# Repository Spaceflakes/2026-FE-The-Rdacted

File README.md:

# WRO-2026

# The Redacted

**The official repository of The Redacted for WRO - Future Engineers 2026**

## Content

### Folders
- **Engineering Manual:** Official manual of team The Redacted for WRO FE 26 (manual.pdf). Contains component selection, CAD, PCB schematics, and assembly guides.
- **PCBA:** Complete set of KiCad PCB files, manufacturing outputs (Gerbers), interactive HTML BOM, and documentation.
- **t-photos:** Team photos (1 formal, 2 informal).
- **v-photos:** 6 photos of the vehicle (front, back, left, right, top, bottom).
- **video:** video.md file with the official vehicle demonstration video link.
- **schemes:** Schematic diagrams, motor connections, power distribution, and 3D PCB renders.
- **src:** ROS 2 control software nodes (motion, LiDAR, camera/vision, parking logic).
- **models:** 3D CAD model files (STEP format).

### Index
- [The Redacted](#the-redacted)
- [Vehicle Photos and Video](#vehicle-photos-and-video)
- [Hardware Materials](#hardware-materials)
- [Mobility Management](#mobility-management)
- [Design](#design)
- [Power Management and Sense Management](#power-management-and-sense-management)
- [Schematic Diagram](#schematic-diagram)
- [Obstacle Management](#obstacle-management)
- [Our Journal](#our-journal)
- [Gantt Chart](#gantt-chart)

---

## The Redacted

### Members
1. **Anvay Jain**  
   Grade 9, The Sanskaar Valley School. Head of this repository. Interested in Space, Science, KSP, and Mathematics.
2. **Siddesh Jain**  
   12th Grader, Billabong High International School. Lead engineer/development head. CAD, hardware, system architecture.
3. **Prayash**  
   Co-engineer and robotics developer. Software integration, testing, and mechanical assembly.

### Team Pictures
#### Formal

#### Informal

---

# Vehicle Photos and Video

### Photos
Vehicle photographs showing all 6 sides are available in the [/v-photos](./v-photos) folder.

### Videos
The demonstration video link and operational breakdown are located in [/video/video.md](./video/video.md).

---

## Hardware Materials

| Name | Link |
| :--- | :--- |
| Rpi 4B/5 | [Link](https://www.raspberrypi.com/products/raspberry-pi-5) |
| LiDAR | [Link](https://robu.in/product/ydlidar-x4-pro-360-degree-ros-scanner-for-navigation-collision-avoidance-10m/#tab-specification) |
| Servo | [Link](https://robu.in/product/surpass-hobby-25kg-s2500m-servo/) |
| Wheels | [Link](https://robu.in/product/65mm-robot-smart-car-12-rim-wheel-blue/) |
| Pi Camera | [Link](https://robu.in/product/arducam-8mp-imx219-175-degree-ultra-wide-angle-raspberry-pi-camera-module-compatible-with-raspberry-pi-4-model-b-pi-3-3b-and-pi-zero-2w/) |
| Custom 2026 WRO Hat PCB | [Link](https://github.com/The-Redacted/WRO-2026/tree/main/PCBA) |
| ESC + Motor | [Link](https://www.hobbywingdirect.com/collections/quicrun-brushless-system/products/quicrun-wp-10bl120-sl-system-g2?variant=41474386854003) |
| Battery | 2x DOGCOM 4S 850 mAh 150C LiPo |
| Gears | Custom 3D Printed Bevel Gears |
| PCB Components | TI LM61460 (5.15V @ 6A) & TPS62932 (8V @ 2A) |
| Carbon Fiber Stock | 12mm OD x 10mm ID Tubes & 3mm OD Rods |

### PCB Design & Prototype PCB
#### Prototype PCB
- **Issue:** Standard 5.0V buck converters caused under-voltage warnings on the Pi 4B under load.
- **Solution:** Designed 2026 WRO Hat for a stabilized 5.15V rail at 6A using the TI LM61460.
- **LC Hot-Plug Fix:** Added a 1000 µF electrolytic capacitor between switch output and GND to dissipate inrush energy and prevent voltage ringing.

#### PCB Design
- **4-Layer Stackup:**
    - Layer 1: High-speed switching/control.
    - Layer 2: Ground plane.
    - Layer 3: Power planes (BATT, 5.15V, 8.0V).
    - Layer 4: Ground plane and secondary signals.

---

## Mobility Management
- **Drive System:** Surpass Hobby 3674 1700KV brushless motor + 120A 4S ESC.
- **Differential Gearbox:** 3D-printed, 2:7 gear reduction ratio.
- **Steering:** Direct-drive Ackerman system with S2500M 25 kg-cm servo on 8V rail.
- **Bearing/Axle Support:** Needle roller/thrust bearings for front knuckles; carbon fiber tubes for rear axles.

---

## Design
- **Wheelbase:** 184.3 mm.
- **Width:** <180 mm.
- **Height:** <80 mm.
- **Chassis:** Carbon fiber rods for structural rigidity.

---

## Power Management and Sense Management

### Power Management
- **Battery:** 2x DOGCOM 4S 850 mAh LiPo in parallel (1700 mAh total).
- **5.15V Rail:** TI LM61460 (6A) for RPi 4B and LiDAR.
- **8.0V Rail:** TI TPS62932 (2A) for steering servo.

### Sense Management
- **YD-LiDAR X4 Pro:** 360° 2D Laser Range Finder for mapping/navigation.
- **Arducam IMX219:** 175° FOV camera for pillar color classification.

---

## Schematic Diagram
- **Power Input:** XT30 connector (14.8V–16.8V).
- **Interfaces:** RPi 4B GPIO, USB (LiDAR), CSI (Camera), Expansion Ports (ToF sensors).

---

## Obstacle Management

### Strategy
Uses ROS 2 for modularity, combining LiDAR for 3D mapping and Camera for 2D pillar color classification.

### Logic
- **Round 1 (Open):** Wall-following via LiDAR and lane maintenance.
- **Round 2 (Obstacle):** Pillar detection -> Camera classification -> Dynamic path planning.
- **Parking:** Automated sequence using LiDAR/Camera boundary detection and PID feedback.

---

## Our Journal
- **June:** Strategy, sensing evaluation, concept sketches.
- **July:** CAD modeling, PCB design, tire molding, printing.
- **August:** Assembly, PCB reflow, ROS 2 software development, documentation.

**The journal is one of the most detailed description and accounts for all the decision made. It should most definitely be read.**

---

## Gantt Chart

| Task / Milestone | June | July | August |
| :--- | :--- | :--- | :--- |
| Concept & Selection | X | | |
| 3D CAD Modeling | | X | |
| KiCad PCB Design | | X | |
| SLA Tire Molds | | X | |
| 3D Print & Assembly | | X | X |
| PCB & Reflow | | | X |
| ROS 2 Software | | | X |
| Integration & Testing | | | X |

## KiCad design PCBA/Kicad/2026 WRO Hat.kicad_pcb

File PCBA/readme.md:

# PCB Design Files

This directory contains the complete set of KiCad Printed Circuit Board (PCB) files, manufacturing outputs, and documentation required to view, modify, assemble, and produce this board.
---

## Directory Contents

Here is a quick overview of the essential files included in this folder:

| File / Folder Name | Type | Description |
| --- | --- | --- |
| **`interactive bom.html`** | HTML | Interactive Bill of Materials tool for easy manual assembly and component placement. |
| **`PCB BOM.csv`** | CSV | The complete, standard Bill of Materials listing all required electronic components, values, and footprints. |
| **`PCB_Schematic.pdf`** | PDF | A high-resolution PDF export of the circuit schematic for quick reference without needing CAD software. |
| **`KiCAD/production/WRO_Hat_V1.5.zip`** | ZIP Archive | The compiled Gerber and Drill files, ready to be uploaded to your favorite PCB manufacturer. |
| **KiCad Source Files** | KiCad | The raw `.kicad_pro`, `.kicad_sch`, and `.kicad_pcb` files for editing the design. |

---

## Detailed File Breakdown

### 1. The Interactive BOM (`interactive bom.html`)

This is a highly useful tool generated by the **InteractiveHtmlBom** plugin. If you plan on soldering this board yourself, simply open this file in any modern web browser. It provides a visual representation of the PCB, allowing you to highlight components, track your progress, and see exactly where each part belongs.

### 2. Standard Bill of Materials (`PCB BOM.csv`)

If you are ordering parts from suppliers like DigiKey, Mouser, or LCSC, this CSV file is your go-to resource. It contains a tabular breakdown of every resistor, capacitor, IC, and connector required.

### 3. Manufacturing Gerbers (`WRO_Hat_V1.5.zip`)

This ZIP archive contains all the industry-standard RS-274X Gerber files and Excellon drill files required by board houses (such as JLCPCB, PCBWay, or OSH Park).

* **Location:** Navigate to the `KiCAD/production/` folder to find this archive.
* **Usage:** Simply upload the `.zip` file directly to the manufacturer's quote page.

### 4. Schematic Reference (`PCB_Schematic.pdf`)

For software engineers writing firmware or hardware reviewers checking pinouts, the PDF schematic offers a clean, easily readable map of the entire circuit. It is fully searchable, making it easy to trace specific signals or power rails.

---

## Getting Started with KiCad

If you want to view or modify the raw board design:

1. Ensure you have the latest version of **KiCad EDA** installed on your system.
2. Clone or download this repository to your local machine.
3. Open the `.kicad_pro` project file in the main directory.
4. Launch the **Schematic Editor** or **PCB Editor** directly from the KiCad project manager.

---

> Important Note: Before sending the Gerber files for manufacturing, please verify that the design meets your specific board house's capabilities and tolerances (minimum trace width, hole size, and clearance).

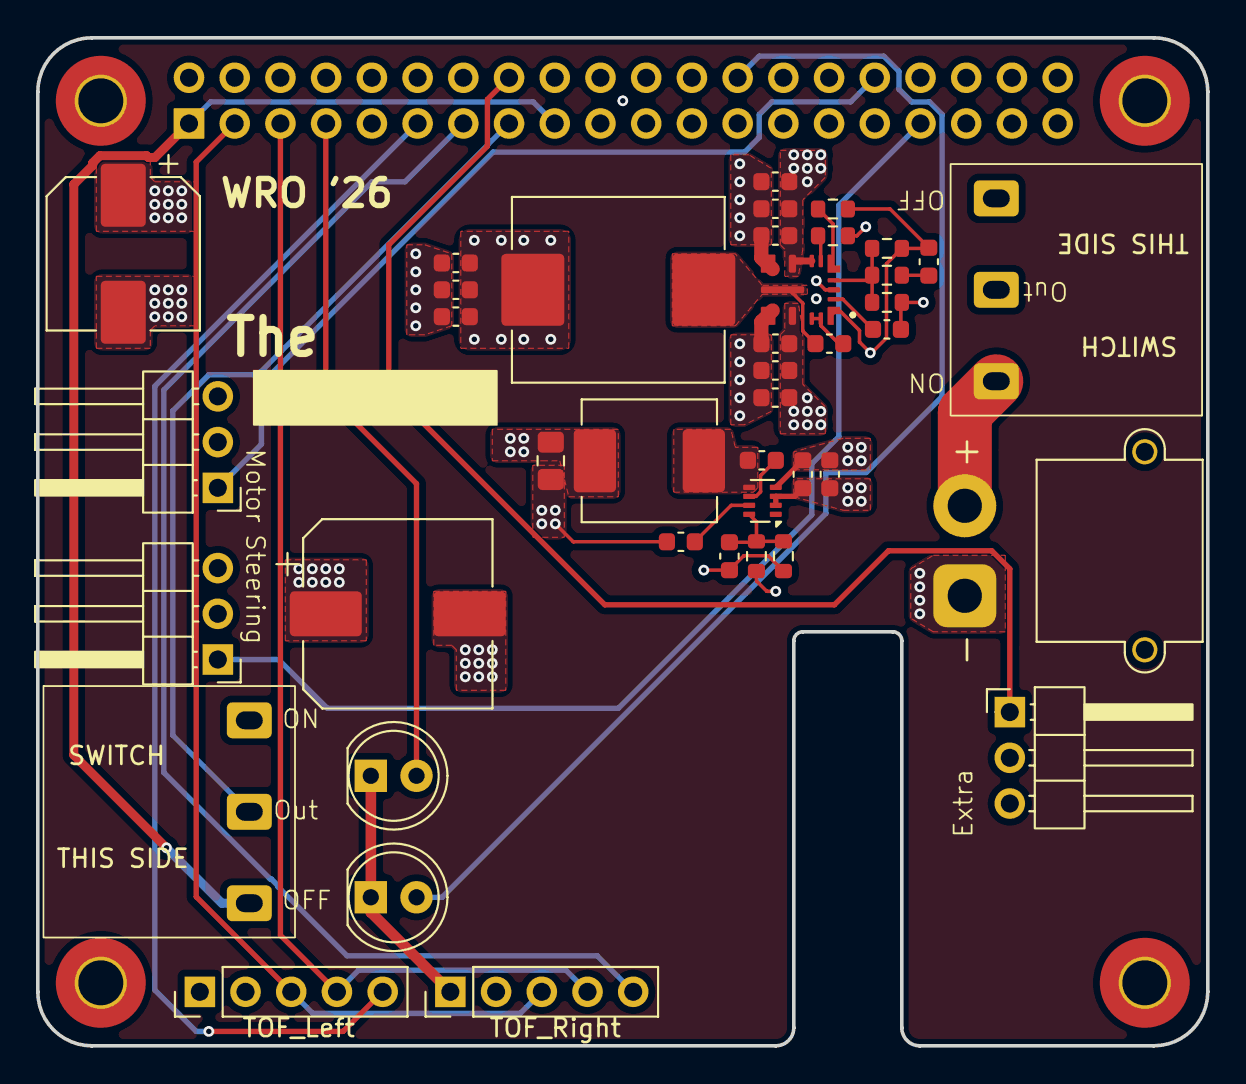
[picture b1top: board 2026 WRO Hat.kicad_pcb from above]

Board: 4 copper layers, 65.0 x 56.0 mm, 46 parts (1 on the bottom side), 27 nets.

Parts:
C1, C2, C3, C4: 4.7u; C_0603_1608Metric
C5, C6, C7: 47u; C_0603_1608Metric
C8, C9: 220n; C_0603_1608Metric
C10: 1u; C_0603_1608Metric
C11: 1p; C_0603_1608Metric
C12, C14, C16: 100n; C_0603_1608Metric
C13: 10u; C_0603_1608Metric
C15: 33n; C_0603_1608Metric
C17: 12p; C_0603_1608Metric
C18: 47u; C_0805_2012Metric_Pad1.18x1.45mm_HandSolder
C19: 220u; CP_Elec_8x10
C20: 270u; CP_Elec_10x10
D1, D2: LED; LED_D5.0mm
H1, H2, H3, H4: MountingHole; MountingHole_2.5mm_Pad_TopBottom
J1: Raspberry_Pi_4; PinSocket_2x20_P2.54mm_Vertical
J2: XT30_Power; AMASS_XT30PW-M_1x02_P2.50mm_Horizontal
J3: TOF_Right; PinHeader_1x05_P2.54mm_Vertical
J4: TOF_Left; PinHeader_1x05_P2.54mm_Vertical
L1: 6.8u; L_Chilisin_BMRF00101040
L2: 15u; L_Chilisin_BMRB00060618
M1: Throttle; PinHeader_1x03_P2.54mm_Horizontal
M2: Steering; PinHeader_1x03_P2.54mm_Horizontal
M3: Extra; PinHeader_1x03_P2.54mm_Horizontal
R1: 32.4k; R_0603_1608Metric
R2, R5: 100k; R_0603_1608Metric
R3: 1k; R_0603_1608Metric
R4: 24.3k; R_0603_1608Metric
R6: 90.9k; R_0603_1608Metric
R7: 10k; R_0603_1608Metric
SW1: POWER; Switch
SW2: Program; Switch
U1: LM61460AFSQRJRRQ1; IC_LM61460AFSQRJRRQ1
U2: TPS62932; SOT-583-8

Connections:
+3V3: J1.1 (3V3), J1.17 (3V3), SW2.3 (C)
+5V: C5.1, C6.1, C7.1, C11.1, C19.1, J1.2 (5V), J1.4 (5V), J3.2, J4.2, L1.2, M3.2 (+), R2.2, R5.2, U1.1 (BIAS)
+8V: C17.1, C18.1, C20.1, L2.2, M2.2 (+), R6.2
+BATT: C1.1, C2.1, C3.1, C4.1, C8.1, C9.1, C13.1, C14.1, SW1.2 (B), U1.7 (EN/SYNC), U1.8 (VIN1), U1.12 (VIN2), U2.2 (EN), U2.3 (VIN)
CRBOOT: C12.2, U1.13 (RBOOT), U1.14 (CBOOT)
GND: C1.2, C2.2, C3.2, C4.2, C5.2, C6.2, C7.2, C8.2, C9.2, C10.1, C13.2, C14.2, C15.1, C18.2, C19.2, C20.2, D1.1 (K), D2.1 (K), J1.6 (GND), J1.9 (GND), J1.14 (GND), J1.20 (GND), J1.25 (GND), J1.30 (GND), J1.34 (GND), J1.39 (GND), J2.1, J3.1, J4.1, M1.3 (-), M2.3 (-), M3.3 (-), R1.1, R4.2, R7.1, SW2.1 (A), U1.3 (AGND), U1.9 (PGND1), U1.11 (PGND2), U2.4 (GND)
unnamed: C11.2, R3.2
unnamed: J2.2, SW1.1 (A)
unnamed: R2.1, R3.1, R4.1, U1.4 (FB)
unnamed: R5.1, U1.5 (PGOOD)
unnamed: R1.2, U1.6 (RT)
unnamed: C12.1, L1.1, U1.10 (SW)
unnamed: C10.2, U1.2 (VCC)
unnamed: C16.1, U2.6 (BST)
unnamed: C17.2, R6.1, R7.2, U2.8 (FB)
unnamed: C15.2, U2.7 (SS)
unnamed: C16.2, L2.1, U2.5 (SW)
SCL: J1.5 (SCL_I2C1/GPIO03), J3.4, J4.4
SDA: J1.3 (SDA_I2C1/GPIO02), J3.3, J4.3
STAT_LED: D1.2 (A), J1.26 (~CE1_SPI0/GPIO07)
STAT_LED_2: D2.2 (A), J1.7 (GPCLK0/GPIO04)
SW1: J1.15 (GPIO22/SDIO_CLK), SW2.2 (B)
Servo1: J1.32 (GPIO12/PWM0), M1.1 (PWM)
Servo2: J1.33 (GPIO13/PWM1), M2.1 (PWM)
Servo3: J1.16 (GPIO23/SDIO_CMD), M3.1 (PWM)
XSHUT1: J1.11 (GPIO17/SPI1_~CE1), J3.5
XSHUT2: J1.13 (GPIO27/SDIO_DAT3), J4.5

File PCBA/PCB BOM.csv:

"Id";"Designator";"Footprint";"Quantity";"Designation";"Supplier and ref";
1;"C1, C2, C3, C4";"C_0603_1608Metric";4;"4.7u";;;
2;"C5, C6, C7, C18";"C_0603_1608Metric";4;"47u";;;
3;"C8, C9";"C_0603_1608Metric";2;"220n";;;
4;"C10";"C_0603_1608Metric";1;"1u";;;
5;"C11";"C_0603_1608Metric";1;"1p";;;
6;"C12, C14, C16";"C_0603_1608Metric";3;"100n";;;
7;"C13";"C_0603_1608Metric";1;"10u";;;
8;"C15";"C_0603_1608Metric";1;"33n";;;
9;"C17";"C_0603_1608Metric";1;"12p";;;
10;"C19";"CP_Elec_8x10";1;"220u";;;
11;"C20";"CP_Elec_10x10";1;"270u";;;
12;"D1";"LED_D5.0mm";1;"LED";;;
13;"J1";"PinSocket_2x20_P2.54mm_Vertical";1;"Raspberry_Pi_4";;;
14;"J2";"AMASS_XT30PW-M_1x02_P2.50mm_Horizontal";1;"XT30_Power";;;
15;"J3";"PinHeader_1x05_P2.54mm_Vertical";1;"TOF_Right";;;
16;"J4";"PinHeader_1x05_P2.54mm_Vertical";1;"TOF_Left";;;
17;"L1";"L_Chilisin_BMRF00101040";1;"6.8u";;;
18;"L2";"L_Chilisin_BMRA00040415";1;"15u";;;
19;"M1";"PinHeader_1x03_P2.54mm_Horizontal";1;"Throttle";;;
20;"M2";"PinHeader_1x03_P2.54mm_Horizontal";1;"Steering";;;
21;"M3";"PinHeader_1x03_P2.54mm_Horizontal";1;"Extra";;;
22;"R1";"R_0603_1608Metric";1;"32.4k";;;
23;"R2, R5";"R_0603_1608Metric";2;"100k";;;
24;"R3";"R_0603_1608Metric";1;"1k";;;
25;"R4";"R_0603_1608Metric";1;"24.3k";;;
26;"R6";"R_0603_1608Metric";1;"90.9k";;;
27;"R7";"R_0603_1608Metric";1;"10k";;;
28;"SW1";"Switch";1;"POWER";;;
29;"SW2";"Switch";1;"Program";;;
30;"U1";"IC_LM61460AFSQRJRRQ1";1;"LM61460AFSQRJRRQ1";;;
31;"U2";"SOT-583-8";1;"TPS62932";;;
